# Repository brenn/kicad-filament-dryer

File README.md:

# Filament dryer

Using an AtMega and old Ender 5 heat plate to make a filament drying box

## Status / TODO

* Gjør ferdig fan deteksjons-krets, signal fra pnp må ti mosfet driver på et hvis

* Discussed with AI regarding 4-pin FAN control and stall detection using diodes, resistor and PNP transistor
https://chatgpt.com/share/6a73b5c4-4dc8-83eb-8aa8-39055729d19b
  * CONCLUSION: Use a buck converter for 24V->13.2v  instead of biased BD139 arrangement to feed the diodes/resistor current detection circuit
  * Cannot use MIC4680-5BM,  AI suggested MCP16331 which is cheap and looks nice
* Can also use the old MC34063 which i have plenty of
  * https://chatgpt.com/share/6a73c253-b44c-83eb-a0b3-313f6cf0aaa1

* Also, discussed with AI on how to implement ADC driven FAN PWM on atmega8
  * https://chatgpt.com/share/6a73b632-64b8-83eb-b409-dc50dc401a8e

# Design 

* Using a Buck converter for 24V-5V conversion
* Using temperature stable LM336, for fun
* Fan inside box runs continously to sirculate air
* Exhaust fan runs briefly every 10th minute to get rid of humidity
* Thermistor in heater is 100k
  * Thermistor value drops pretty fast above 25 degrees
  * I want accuracy when bed temp > 80 degrees
  * To improve accuracy in temperature range of interest a 47k resistor is used in the divider
* Thermistor is a simple glass rod type of 10k@25 degrees
    * I want accuracy when box temp is 50-80 degrees
    * Using a 4.7k resistor in divider (instead of 10k)
* Using small Pololu LCD in 4-bit mode, scrapped from old bots
*

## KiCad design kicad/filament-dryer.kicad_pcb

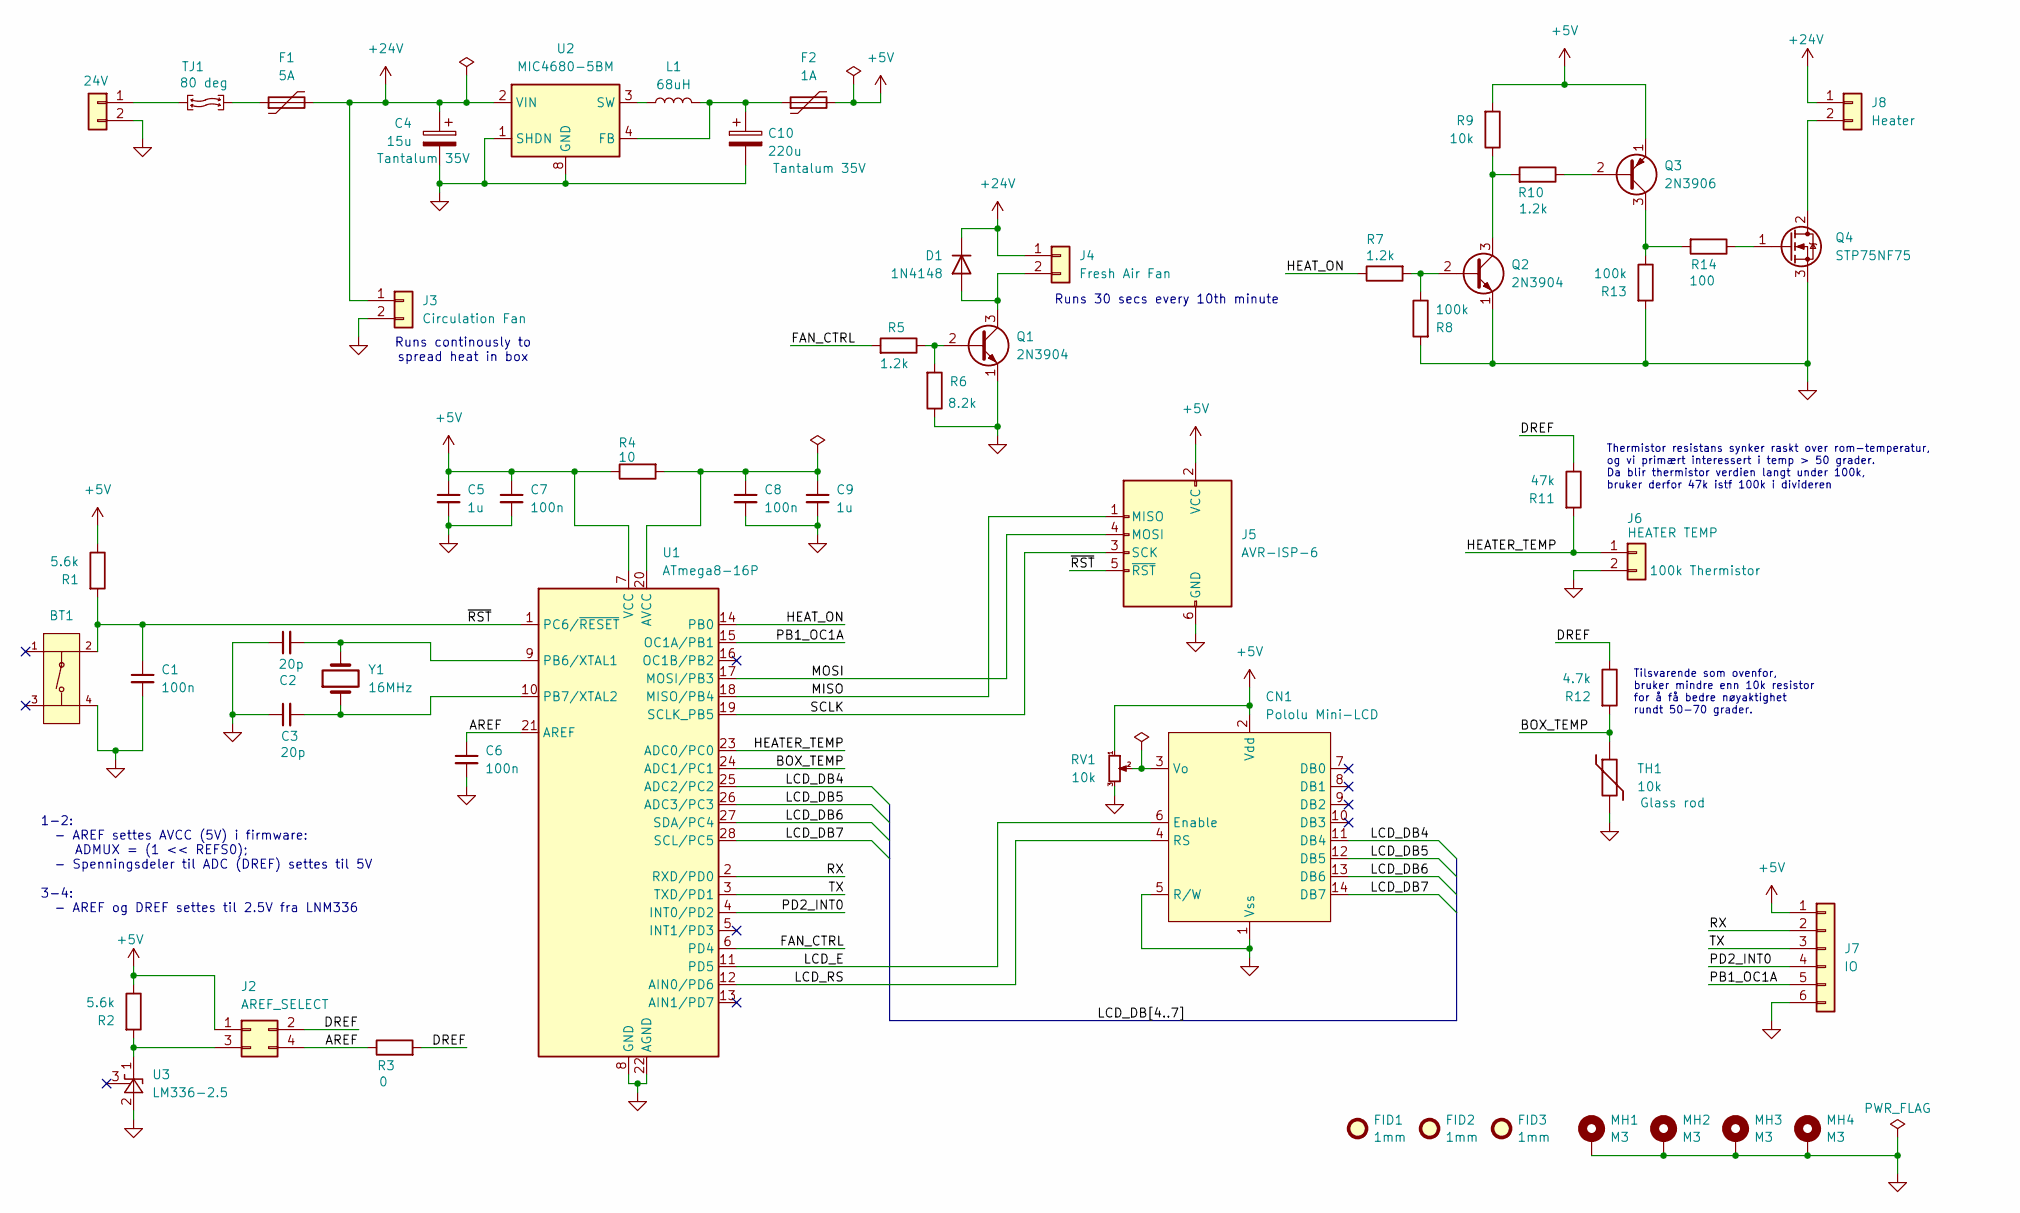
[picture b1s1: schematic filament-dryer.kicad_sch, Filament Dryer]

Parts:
BT1: Tactile Button; PushButton-SMD_4P-L5.1-W5.1; Voltage Rating (Dc) 12V; Part TS-1187A-B-A-B; LCSC C318884
C1, C6, C7, C8: 100n; C_Disc_D4.3mm_W1.9mm_P5.00mm
C2, C3: 20p; C_Disc_D4.3mm_W1.9mm_P5.00mm
C4: 15u; CP_EIA-6032-28_Kemet-C
C5, C9: 1u; CP_EIA-6032-20_AVX-F
C10: 220u; CP_EIA-6032-28_Kemet-C
CN1: Pololu Mini-LCD; PinHeader_2x07_P2.54mm_Vertical
D1: 1N4148; D_DO-35_SOD27_P7.62mm_Horizontal
F1: 5A; FuseHolder_20x5mm
F2: 1A; Fuse_1206_3216Metric_Pad1.42x1.75mm_HandSolder
FID1, FID2, FID3: 1mm; Fiducial_1mm_Mask2mm
J1: 24V; TerminalBlock_2_P5.08mm
J2: AREF_SELECT; PinHeader_2x02_P2.54mm_Vertical
J3: Circulation Fan; PinHeader_1x02_P2.54mm_Vertical
J4: Fresh Air Fan; PinHeader_1x02_P2.54mm_Vertical
J5: AVR-ISP-6; PinHeader_2x03_P2.54mm_Vertical
J6: HEATER TEMP; JST_PH_B2B-PH-K_1x02_P2.00mm_Vertical
J7: IO; PinHeader_1x06_P2.54mm_Vertical
J8: Heater; TerminalBlock_2_P5.08mm
L1: 68uH; L_12x12mm_H6mm
MH1, MH2, MH3, MH4: M3; MountingHole_3.2mm_M3_Pad_Via
Q1, Q2: 2N3904; TO-92_Inline
Q3: 2N3906; TO-92_Inline
Q4: STP75NF75; TO-220-3_Vertical
R1, R2: 5.6k; R_Axial_DIN0207_L6.3mm_D2.5mm_P10.16mm_Horizontal
R3: 0; R_Axial_DIN0207_L6.3mm_D2.5mm_P10.16mm_Horizontal
R4: 10; R_Axial_DIN0207_L6.3mm_D2.5mm_P10.16mm_Horizontal
R5, R7, R10: 1.2k; R_Axial_DIN0207_L6.3mm_D2.5mm_P10.16mm_Horizontal
R6: 8.2k; R_Axial_DIN0207_L6.3mm_D2.5mm_P10.16mm_Horizontal
R8, R13: 100k; R_Axial_DIN0207_L6.3mm_D2.5mm_P10.16mm_Horizontal
R9: 10k; R_Axial_DIN0207_L6.3mm_D2.5mm_P10.16mm_Horizontal
R11: 47k; R_Axial_DIN0207_L6.3mm_D2.5mm_P10.16mm_Horizontal
R12: 4.7k; R_Axial_DIN0207_L6.3mm_D2.5mm_P10.16mm_Horizontal
R14: 100; R_Axial_DIN0207_L6.3mm_D2.5mm_P10.16mm_Horizontal
RV1: 10k; Potentiometer_VANXY_T73YP_Vertical
TH1: 10k; R_Axial_DIN0207_L6.3mm_D2.5mm_P10.16mm_Horizontal
TJ1: 80 deg; SolderWire-0.75sqmm_1x02_P7mm_D1.25mm_OD3.5mm
U1: ATmega8-16P; DIP-28_W7.62mm
U2: MIC4680-5BM; SOIC-8_3.9x4.9mm_P1.27mm
U3: LM336-2.5; TO-92L_Inline
Y1: 16MHz; Crystal_HC49-4H_Vertical

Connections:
+5V: C5.1, C7.1, CN1.2 (Vdd), F2.2, J2.1, J5.2 (VCC), J7.1, Q3.1 (E), R1.1, R2.1, R4.1, R9.2, RV1.1, U1.7 (VCC)
+24V: C4.1, D1.1 (K), F1.2, J3.1, J4.1, J8.1, U2.2 (VIN)
/AREF: C6.1, J2.4, R3.1, U1.21 (AREF)
/BOX_TEMP: R12.2, TH1.1, U1.24 (ADC1/PC1)
/DREF: J2.2, R3.2, R11.1, R12.1
/FAN_CTRL: R5.2, U1.6 (PD4)
/HEATER_TEMP: J6.1, R11.2, U1.23 (ADC0/PC0)
/HEAT_ON: R7.1, U1.14 (PB0)
/LCD_DB4: CN1.11 (DB4), U1.25 (ADC2/PC2)
/LCD_DB5: CN1.12 (DB5), U1.26 (ADC3/PC3)
/LCD_DB6: CN1.13 (DB6), U1.27 (SDA/PC4)
/LCD_DB7: CN1.14 (DB7), U1.28 (SCL/PC5)
/LCD_E: CN1.6 (Enable), U1.11 (PD5)
/LCD_RS: CN1.4 (RS), U1.12 (AIN0/PD6)
/MISO: J5.1 (MISO), U1.18 (MISO/PB4)
/MOSI: J5.4 (MOSI), U1.17 (MOSI/PB3)
/PB1_OC1A: J7.5, U1.15 (OC1A/PB1)
/PD2_INT0: J7.4, U1.4 (INT0/PD2)
/RX: J7.2, U1.2 (RXD/PD0)
/SCLK: J5.3 (SCK), U1.19 (SCLK_PB5)
/TX: J7.3, U1.3 (TXD/PD1)
/~RST: BT1.2 (B), C1.1, J5.5 (~RST), R1.2, U1.1 (PC6/~RESET)
unnamed: CN1.3 (Vo), RV1.2
unnamed: D1.2 (A), J4.2, Q1.3 (C)
unnamed: J1.1, TJ1.1 (Pin1)
unnamed: J2.3, R2.2, U3.1 (K)
unnamed: J8.2, Q4.2 (D)
unnamed: Q1.2 (B), R5.1, R6.2
unnamed: Q2.2 (B), R7.2, R8.1
unnamed: Q2.3 (C), R9.1, R10.2
unnamed: Q3.2 (B), R10.1
unnamed: Q3.3 (C), R13.1, R14.2
unnamed: Q4.1 (G), R14.1
unnamed: F1.1, TJ1.2 (Pin2)
unnamed: C8.1, C9.1, R4.2, U1.20 (AVCC)
unnamed: C2.2, U1.9 (PB6/XTAL1), Y1.2
unnamed: C3.2, U1.10 (PB7/XTAL2), Y1.1
unnamed: C10.1, F2.1, L1.2, U2.4 (FB)
unnamed: L1.1, U2.3 (SW)

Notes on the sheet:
1-2: - AREF settes AVCC (5V) i firmware: ADMUX = (1 << REFS0); - Spenningsdeler til ADC (DREF) settes til 5V 3-4: - AREF og DREF settes til 2.5V fra LNM336
Runs continously to spread heat in box
Tilsvarende som ovenfor, bruker mindre enn 10k resistor for å få bedre nøyaktighet rundt 50-70 grader.
Runs 30 secs every 10th minute
Thermistor resistans synker raskt over rom-temperatur, og vi primært interessert i temp > 50 grader. Da blir thermistor verdien langt under 100k, bruker derfor 47k istf 100k i divideren

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
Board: 2 copper layers, 56 parts (0 on the bottom side), 40 nets, no tracks yet.
